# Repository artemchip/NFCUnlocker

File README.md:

# Разблокировка ПК с помощью NFC-чипов и/или бесконтактных карт
Работает как эмулятор клавиатуры.  
Устройство:   

Демонстрация работы - видео Demo.mp4

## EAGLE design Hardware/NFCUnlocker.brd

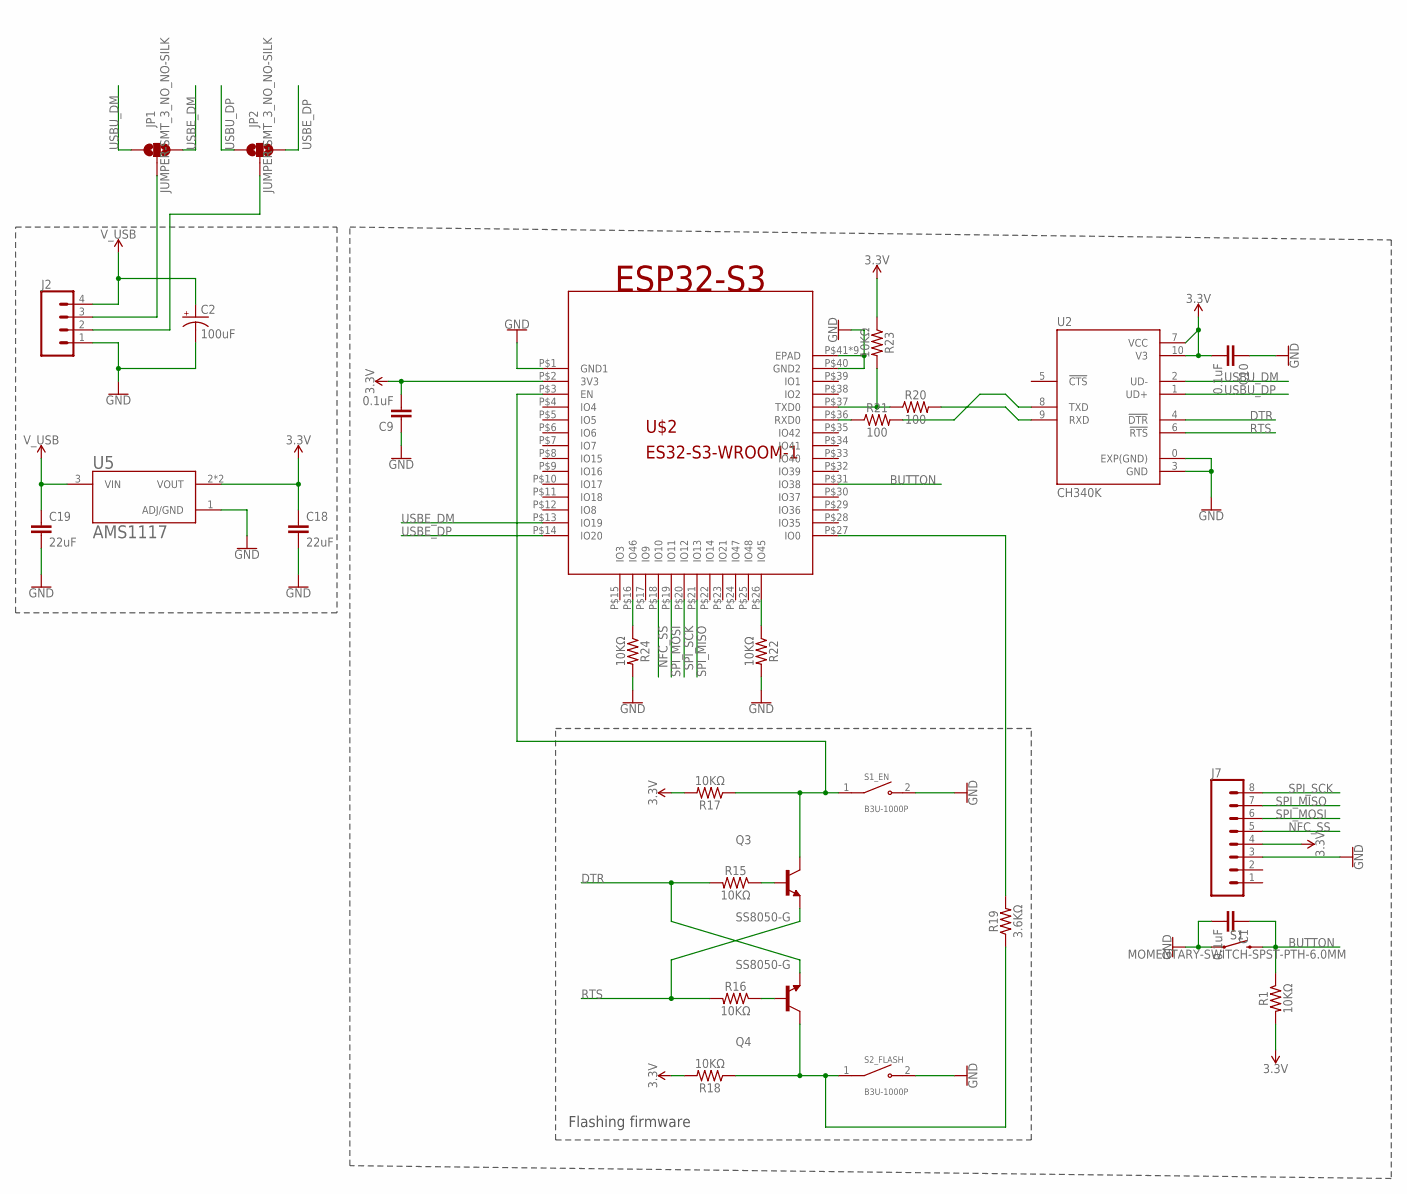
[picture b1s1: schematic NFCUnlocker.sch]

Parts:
C1, C9, C10: 0.1uF; 0402
C2: 100uF; CPOL-RADIAL-2.5MM-6.5MM
C18, C19: 22uF; 1206
J2: CONN_04LONGPADS; 1X04_LONGPADS
J7: CONN_08LONGPADS; 1X08_LONGPADS
JP1, JP2: JUMPER-SMT_3_NO_NO-SILK; SMT-JUMPER_3_NO_NO-SILK
Q3, Q4: SS8050-G; TRANS_SS8050-G
R1, R15, R16, R17, R18, R22, R23, R24: 10KΩ; 0402-TIGHT
R19: 3.6KΩ; 0402-TIGHT
R20, R21: 100; 0402-TIGHT
S1: MOMENTARY-SWITCH-SPST-PTH-6.0MM; TACTILE_SWITCH_PTH_6.0MM
S1_EN, S2_FLASH: B3U-1000P; SW_B3U-1000P
U2: CH340K; SOP100P600X160-11N
U5: AMS1117; SOT229P700X180-4N
U$2: ES32-S3-WROOM-1; ESP32-S3-WROOM-1

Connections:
3.3V: C9.2, C10.2, C18.1, J7.4, R1.2, R17.2, R18.2, R23.1, U2.7 (VCC), U2.10 (V3), U5.2 (VOUT), U5.4 (VOUT), U$2.P$2 (3V3)
BUTTON: C1.1, R1.1, S1.3 (2), U$2.P$31 (IO38)
DTR: Q4.2 (E), R15.2, U2.4 (!DTR)
GND: C1.2, C2.2 (-), C9.1, C10.1, C18.2, C19.2, J2.1, J7.3, R22.2, R24.2, S1.1, S1_EN.2, S2_FLASH.2, U2.0 (EXP(GND)), U2.3 (GND), U5.1 (ADJ/GND), U$2.P$1 (GND1), U$2.P$40 (GND2), U$2.P$41 (EPAD), U$2.P$42 (EPAD), U$2.P$43 (EPAD), U$2.P$44 (EPAD), U$2.P$45 (EPAD), U$2.P$46 (EPAD), U$2.P$47 (EPAD), U$2.P$48 (EPAD), U$2.P$49 (EPAD)
unnamed: J2.3, JP1.2
unnamed: J2.2, JP2.2
unnamed: R20.2, U2.9 (RXD)
unnamed: R21.2, U2.8 (TXD)
unnamed: R20.1, R23.2, U$2.P$37 (TXD0)
unnamed: R21.1, U$2.P$36 (RXD0)
unnamed: Q4.1 (B), R16.1
unnamed: Q3.1 (B), R15.1
unnamed: R19.2, U$2.P$27 (IO0)
unnamed: Q3.3 (C), R17.1, S1_EN.1, U$2.P$3 (EN)
unnamed: Q4.3 (C), R18.1, R19.1, S2_FLASH.1
unnamed: R24.1, U$2.P$16 (IO46)
unnamed: R22.1, U$2.P$26 (IO45)
NFC_SS: J7.5, U$2.P$18 (IO10)
RTS: Q3.2 (E), R16.2, U2.6 (!RTS)
SPI_MISO: J7.7, U$2.P$21 (IO13)
SPI_MOSI: J7.6, U$2.P$19 (IO11)
SPI_SCK: J7.8, U$2.P$20 (IO12)
USBE_DM: JP1.3, U$2.P$13 (IO19)
USBE_DP: JP2.3, U$2.P$14 (IO20)
USBU_DM: JP1.1, U2.2 (UD-)
USBU_DP: JP2.1, U2.1 (UD+)
V_USB: C2.1 (+), C19.1, J2.4, U5.3 (VIN)

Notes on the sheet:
Flashing firmware

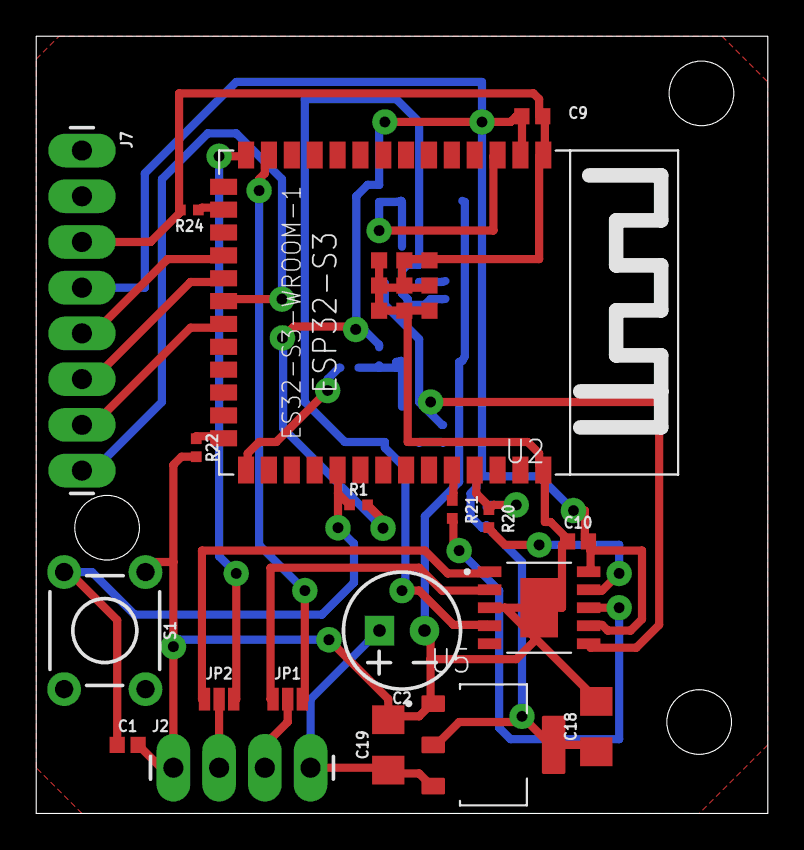
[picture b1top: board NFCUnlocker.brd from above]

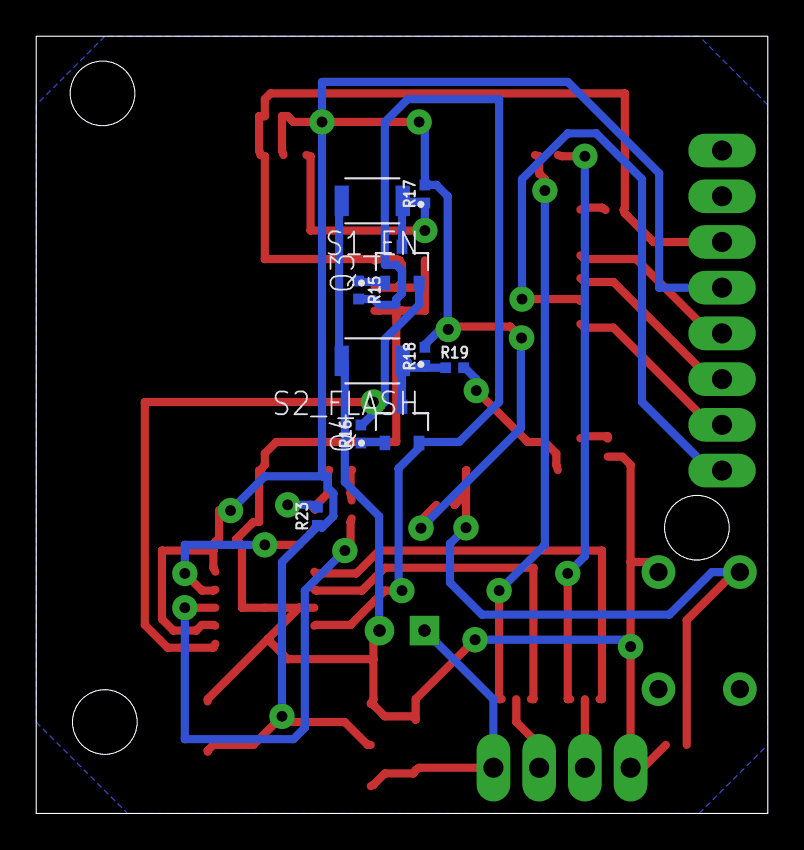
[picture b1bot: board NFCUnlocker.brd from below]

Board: 2 copper layers, 40.6 x 43.2 mm, 29 parts (10 on the bottom side), 27 nets.

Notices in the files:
parts and their libraries:
SparkFun-Capacitors: Licensing: Creative Commons ShareAlike 4.0 International - https://creativecommons.org/licenses/by-sa/4.0
